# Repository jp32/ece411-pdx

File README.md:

# Automated Plant Watering Device

This project enables the watering of indoor house plants without being physically present. As various plants need different watering levels, a knob (actually a potentiometer) is set by the user to determine the amount of time to water the plant, which can be set between 5 to 30 seconds. A mositure sensor is used to monitor the soil, in which water is automatically dispensed when the soil is near dry.

## Prerequisites

Boards are pre-installed with the lastest firmware. To upload the test bench firmware the latest version of the Arduino IDE is recommended (free and can be downloaded [here](https://www.arduino.cc/en/Main/Software)).

## Built With
* [Arduino](https://www.arduino.cc/en/Main/Software) - Integrated development environment
* [EAGLE](https://www.autodesk.com/products/eagle/overview) - Schematic and board layout
* [LTspice](https://www.analog.com/en/design-center/design-tools-and-calculators/ltspice-simulator.html) - Circuit simulation
* [GitHub](https://github.com/) - Version control and team collaboration

## Authors

* **Justin Patterson**
* **Jonathan Lampman**
* **Jian Meng**
* **Bruno Duergon**

## License

This project is licensed under the GNU General Public License - see the [LICENSE](LICENSE) file for details

## Acknowledgements
* **Portland State University ECE Department**
* **Andrew Greenberg**
* **Eric Ruhl**

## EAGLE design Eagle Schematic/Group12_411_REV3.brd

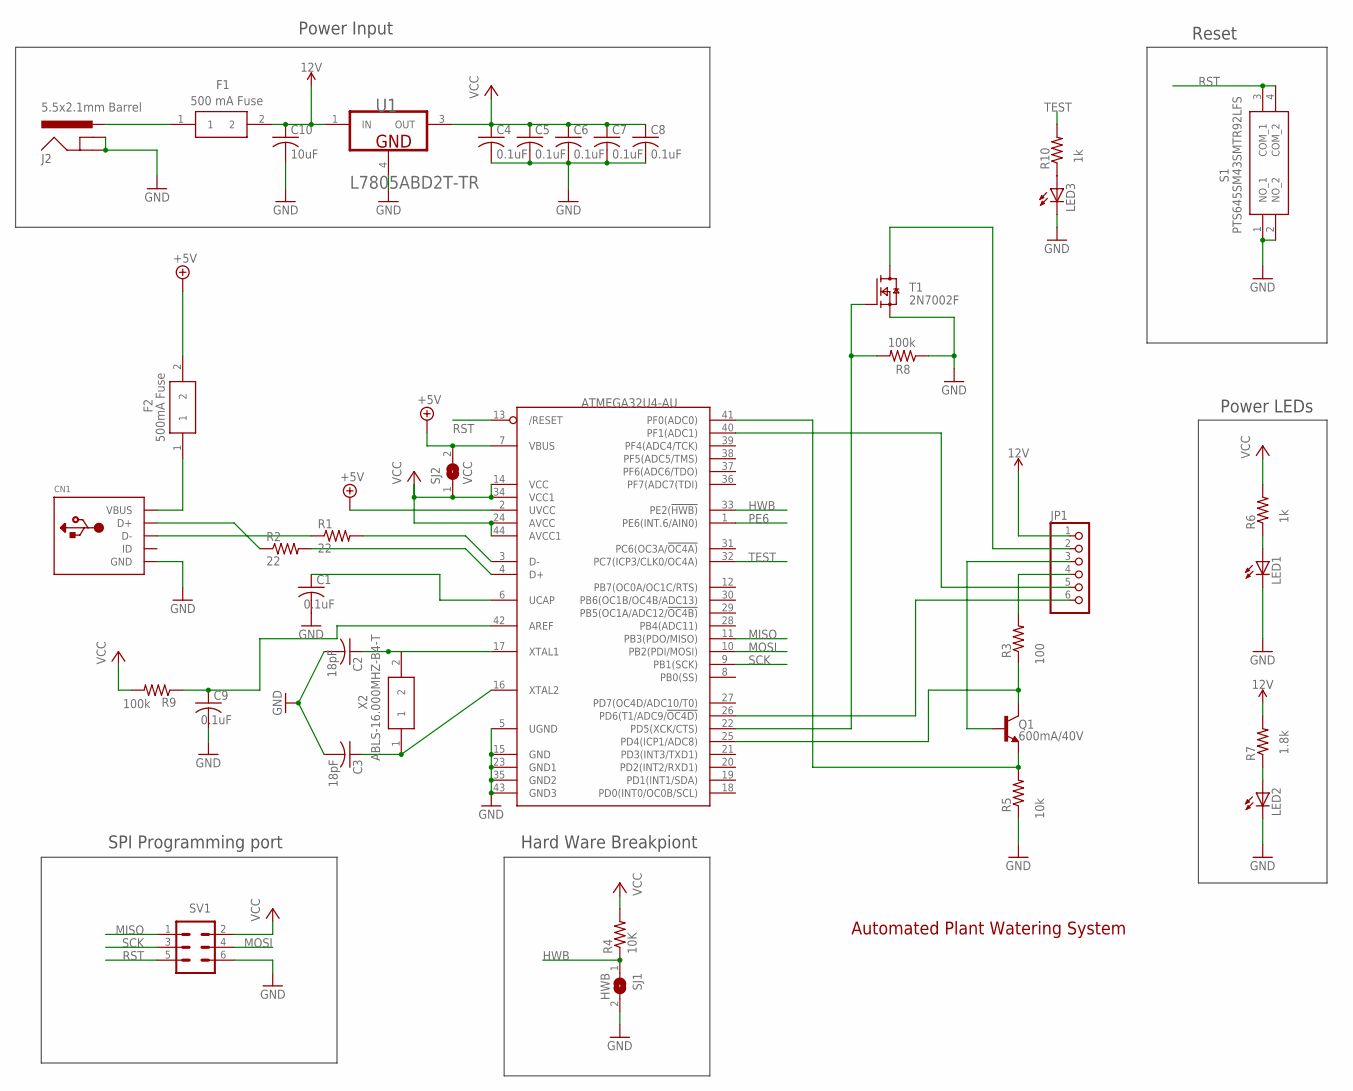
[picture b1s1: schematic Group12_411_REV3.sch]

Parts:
C1, C4, C5, C6, C7, C8, C9: 0.1uF; C0805K
C2, C3: 18pF; C0805K
C10: 10uF; C0805K
CN1: USBMINIB; USB-MINIB
F1: MFU0805FF00500P100; FUSC2012X55N; MANUFACTURER_PART_NUMBER 500 mA Fuse
F2: MFU0805FF00500P100; FUSC2012X55N; MANUFACTURER_PART_NUMBER 500mA Fuse
J2: 5.5x2.1mm Barrel; POWER_JACK_SMD
JP1: PINHD-1X6-3.5MM; 1X06-3.5MM
LED1, LED2, LED3: LEDCHIP-LED0603; CHIP-LED0603
Q1: 600mA/40V; SOT23-3
R1, R2, R3, R5: 22; R0805
R4, R6, R7, R8, R10: 10K; R0805
R9: 100k; R0805
S1: PTS645SM43SMTR92LFS; PTS645SMT
SJ1: HWB; SJ
SJ2: VCC; SJ
SV1: MA03-2
T1: 2N7002F; SOT23
U1: STMICROELECTRONICS_L7805ABD2T-TRSTMICROELECTRONIC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; STMICROELECTRONICS_L7805ABD2T-TR_0
U2: ATMEGA32U4-AU; TQFP44
X2: ABLS-16.000MHZ-B4-T; ABLS

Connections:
12V: C10.1, F1.2, JP1.1, R7.2, U1.1 (IN)
+5V: F2.2, SJ2.2, U2.2 (UVCC), U2.7 (VBUS)
GND: C1.2, C2.2, C3.2, C4.2, C5.2, C6.2, C7.2, C8.2, C9.2, C10.2, CN1.GND, J2.GND (GNDBREAK), J2.P$4 (GND), LED1.C, LED2.C, LED3.C, R5.1, R8.1, S1.1 (NO_1), S1.2 (NO_2), SJ1.2, SV1.6, T1.2 (S), U1.4 (GND), U2.5 (UGND), U2.15 (GND), U2.23 (GND1), U2.35 (GND2), U2.43 (GND3)
HWB: R4.1, SJ1.1, U2.33 (PE2(!HWB))
MISO: SV1.1, U2.11 (PB3(PDO/MISO))
MOSI: SV1.4, U2.10 (PB2(PDI/MOSI))
unnamed: LED3.A, R10.1
unnamed: CN1.D+, R2.1
unnamed: JP1.4, R3.2
unnamed: R2.2, U2.4 (D+)
unnamed: CN1.D-, R1.1
unnamed: C1.1, U2.6 (UCAP)
unnamed: R1.2, U2.3 (D-)
unnamed: C2.1, U2.17 (XTAL1), X2.2
unnamed: C3.1, U2.16 (XTAL2), X2.1
unnamed: LED1.A, R6.1
unnamed: Q1.3 (C), R3.1, U2.25 (PD4(ICP1/ADC8))
unnamed: Q1.2 (E), R5.2, U2.41 (PF0(ADC0))
unnamed: JP1.3, Q1.1 (B)
unnamed: JP1.2, T1.3 (D)
unnamed: LED2.A, R7.1
unnamed: F1.1, J2.VIN0 (PWR)
unnamed: CN1.VBUS, F2.1
unnamed: R8.2, T1.1 (G), U2.22 (PD5(XCK/CTS))
unnamed: JP1.5, U2.40 (PF1(ADC1))
unnamed: JP1.6, U2.26 (PD6(T1/ADC9/!OC4D))
unnamed: C9.1, R9.1, U2.42 (AREF)
PE6: U2.1 (PE6(INT.6/AIN0))
RST: S1.3 (COM_1), S1.4 (COM_2), SV1.5, U2.13 (/RESET)
SCK: SV1.3, U2.9 (PB1(SCK))
TEST: R10.2, U2.32 (PC7(ICP3/CLK0/OC4A))
VCC: C4.1, C5.1, C6.1, C7.1, C8.1, R4.2, R6.2, R9.2, SJ2.1, SV1.2, U1.3 (OUT), U2.14 (VCC), U2.24 (AVCC), U2.34 (VCC1), U2.44 (AVCC1)

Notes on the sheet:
Automated Plant Watering System
Power Input
Reset
Power LEDs
SPI Programming port
Hard Ware Breakpiont

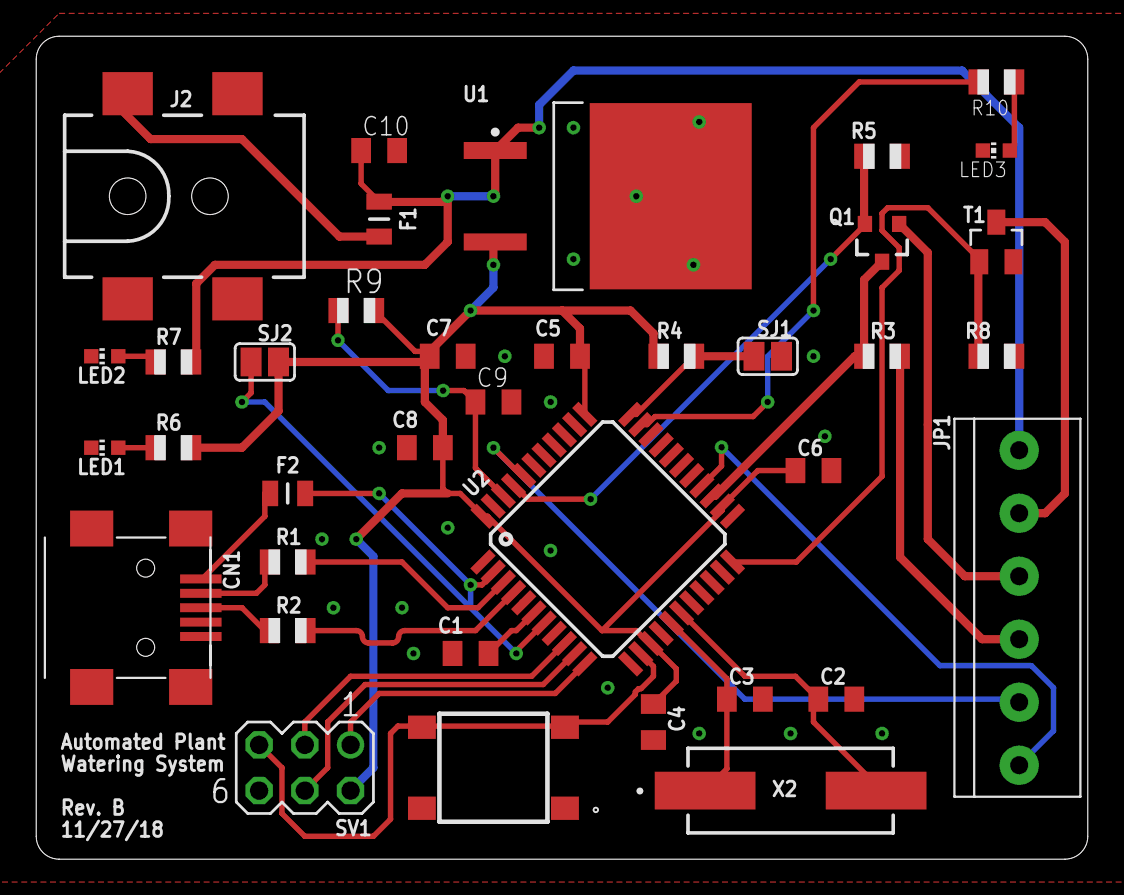
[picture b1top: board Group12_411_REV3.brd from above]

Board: 2 copper layers, 58.4 x 45.7 mm, 37 parts (0 on the bottom side), 31 nets.

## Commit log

2018-10-11 Add ATmega328P datasheet
2018-10-13 Add User Guide for AVR Dragon
    Programmer and Debugger in Capstone Lab
2018-10-15 Add pic for ATmega328-32P pinout
2018-10-23 Create Eagle Schematic
    All Times Eagle CAD
2018-10-23 Create Eagle Schematic
    All Things Eagle
2018-10-23 Create Eagle Schematic
2018-10-23 Ohhh
    Yeahhhh
2018-10-23 Create Eagle Schematic
    looooo
2018-10-23 Create Eagle Schematic
    sdf
2018-10-23 Create Poop on Your Shoe
    dfad
2018-10-24 removed the shit
2018-10-24 Still needs work on the Programming Dongle
2018-10-24 Schematic Still needs work on the Programming Dongle
2018-10-24 .s#1 file
2018-10-25 Eagle Schematic turned In on 10/25
2018-10-25 Added the Product Design Specifications
2018-10-25 Block_Diagram_Draft
2018-10-29 Code for Arduino Bootloader
    Credit to Nick Gammon. Instructions at https://www.gammon.com.au/bootloader
2018-10-30 Add block diagram to PDS
2018-11-05 Rev1
2018-11-05 Add ATMega32u4 Datasheet
2018-11-09 Added Switch
2018-11-09 Add Catarina-Leonardo bootloader
2018-11-09 Add L78 voltage regulator datasheet
2018-11-11 Updated BOM and New Eagle Schematic
2018-11-12 Added d2pak for linear reg
2018-11-12 Changed Q1 to SMD
2018-11-12 Update switch in BOM
2018-11-12 LED updated
2018-11-12 Changed power transistor
2018-11-12 Add fuse to BOM
2018-11-12 Added r
2018-11-12 General updates
2018-11-13 Updated Eagle
2018-11-13 Eagle lbr
2018-11-13 For realllllzz
2018-11-13 eagle shiz
2018-11-15 Cross your fingers
2018-11-15 BOM for digikey
2018-11-26 Decision Matrix Added
2018-11-28 Update Eagle Schematic and Board
    Connect +5V on board, and add a programmable LED on pin 32 for testing
2018-11-28 Useful Documents
2018-11-28 Add block level diagrams
    In progress
2018-11-29 Updated block diagram
2018-11-30 Updated block diagram V2
2018-12-01 Arduino_Code V0.9
2018-12-02 Boundary level updated
2018-12-02 Finished Deliverables
2018-12-03 Code Update
2018-12-05 Testbench code
2018-12-05 Changed valve stuff (test)
2018-12-05 Test for Bruno
2018-12-05 Code is all up to date
2018-12-05 Finished testbench
2018-12-05 Update testbench code
2018-12-05 Added presentation and sensorvalue > 100
2018-12-06 Stff
2018-12-06 Add sensor test for testbench
2018-12-06 Final code
2018-12-06 eagle png
2018-12-06 mhmm
2018-12-06 Lowkey
2018-12-06 Yeet
2018-12-06 Finishing up presentation
2018-12-06 Dev branch file clean-up
2018-12-06 Master file clean-up
2018-12-06 Final presentation cleanup and changes
2018-12-06 Finalized presentation with gantt chart

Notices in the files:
parts and their libraries:
SparkFun-Connectors: Licensing: Creative Commons ShareAlike 4.0 International - https://creativecommons.org/licenses/by-sa/4.0
NXP_60_26022015: This library may be distributed and adapted freely for any purpose, as long as NXP is credited and any new creation is licensed under the same terms.
